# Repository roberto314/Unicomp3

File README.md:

# UNICOMP #

Version 3.00

A modular 8-bit Computer able to recreate (nearly) every microcomputer of the mid 70s to early 80s 
in Hardware without FPGAs (although an FPGA can be added). Can also be used as a teaching tool for:

* VHDL or Verilog
* C
* RTOS (STM32F401 runs ChibiOS. Link: https://www.chibios.org)
* Python
* bash and linux in general (Olimex board runs linux with fbterm and tmux)
* Harwaredesign
* Timing of CPUs
* maybe Assembler
* SPI and I2C Interfaces
* CPLDs and FPGAs

It is different from other designs because of these points:

* it uses a 3.3V only Bus,
* it uses fast RAM for 16 chipselect outputs with single address resolution over the whole 1MB range,
* it uses one SRAM for RAM and ROM replacement (can be write writeprotected) with 1MB,
* it uses a clock generator chip (DS1085) - no more crystals to change,
* it is configureable via STM32 (RAM and ROM content, Clock frequency, chip select lines),
* it can program the CPLDs (only XC9572 and XC9536 tested) from the STM32, no external programmer needed.
* Board size is 100mm x 100mm - no backplane (like the PC/104 standard. Link: https://en.wikipedia.org/wiki/PC/104).
* and maybe most convenient: it can change RAM and ROM content on the fly without crashing the CPU. 
  For example starting the Apple I, going into Basic and uploading the program in about half a second is really nice.

Unicomp plus Logic Analyzer:

### Unicomp modules ###

* USB-Serial board:
	- a simple board with an universal 4x USB to UART module from ebay (FT4232).

* CPU board:
	- can be any 8-bit CPU (6502, 6802, 6809, 68008, 6803, 8051,...)
	- a CPLD (XC9572) for clock generation and glue logic

* Multi Serial boaŕd:
	- suggested chip select #0
	- can be used with the following serial interface chips: MC6850, MOS6551, MOS6552 or pin compatible

* Multi Parallel boaŕd:
	- suggested chip select #1
	- can be used with the following parallel interface chips: MC6820, MC6821, MOS6520, MOS6521, MOS6522, MOS6526, MOS8520, MOS6532 in the first slot
    - the first slot can additionally mimic a MOS6530
	- the second slot can accommodate a MOS6522 or pin compatible

* RAMROM board:
	- chip select fixed at #15 (for chipselect RAM or ROM) and #14 for Write Disable (High for ROM),
	- 1M of SRAM plus an extra 16-bit RAM for address decoding,
	- a STM32F401 'blackpill' board to fill the SRAMs with data over USB,
	- USB shell on the STM32 to change ROM content on the fly,
	- also configures the Address Range of all peripheral modules,
	- acts as a XSVF Player to program the CPLDs

* Prototype board:
	- empty board for prototyping
	- no CPLD

* MAX-II (EPM240) board:
	- CPLD plus Buffers

* self made module:
	- chip select can be any non-used line in the Range from 0 to 13.
	- size is 100mm x 100mm
	- there is the prototype board in the repository for the position of the connectors and also the labels (pinout)

### Configuration RAM ###

The configuration is done with 1Mx16 fast ram on the RAMROM board. It is configured from the STM32F401.
The cs = 15 is for writing the main RAM, cs = 14 is the Write Disable.
The rest is free.

### Working Recreations of old computers (tested again with Unicomp3) ###

| Name                     | prim. IO    | chips used                    | os                               | weblink                                                                 |
|--------------------------|-------------|-------------------------------|----------------------------------|-------------------------------------------------------------------------|
| Motorola MEK D2          | serial      | MC6802, MĆ6850                | newbug, xswtbug, mondeb          |Link: https://www.retrotechnology.com/restore/smithbug.html              |
| Motorola MEK D1          | serial      | MC6802, MĆ6821 (plus Arduino) | Mikbug                           |Link: https://www.retrotechnology.com/restore/smithbug.html              |
| SWTPC 6800               | serial      | MC6802, MĆ6821 (plus Arduino) | Mikbug                           |Link: https://deramp.com/swtpc.com/                                      |
| SWTPC 6800               | serial      | MC6802, MĆ6850                | SWTBUG, SWTBUGA, Mondeb, xSWTBUG |Link: https://deramp.com/swtpc.com/                                      |
| Heathkit ET3400          | serial      | MC6802, MĆ6850                | MITS BASIC, TSC MicroBASIC,...   |Link: https://github.com/jefftranter                                     |
| HD6303 Board (Eric Klaus)| serial      | HD6303 or MC6803              | Monitor +BASIC                   |Link: https://sites.google.com/site/ericmklaus/projects-1/hd6303cpuboard |
| MC3 Computer             | serial      | HD6303 or MC6803              | Monitor                          |Link: https://www.waveguide.se/?article=mc3-a-diy-8-bit-computer         |
| Grant Searle 6809 board  | serial      | MC6809E, MC6850               | MS Basic                         |Link: http://searle.x10host.com/6809/Simple6809.html                     |
| Grant Searle 6502 board  | serial      | MOS6502, MC6850               | OSI Basic                        |Link: http://searle.x10host.com/6502/Simple6502.html                     |
| Daryl Rictor 6502 board  | serial      | MOS6502, R6551                | SBC-2 (monitor only)             |Link: https://sbc.rictor.org/info2.html                                  |
| Daryl Rictor 6502 board  | serial      | MOS6502, MC6850               | SBC-2 (monitor only)             |Link: https://sbc.rictor.org/info2.html                                  |
| SYM1                     | serial      | MOS6502, UM6532               | SYM1 ( +BASIC +RAE)              |Link: http://retro.hansotten.nl/6502-sbc/synertek-sym-ktm/sym-1/         |
| KIM1                     | serial      | MOS6502, UM6532               | KIM1                             |Link: http://retro.hansotten.nl/6502-sbc/kim-1-manuals-and-software/     |
| Apple I                  | serial      | MOS6502, MĆ6821 (plus Arduino)| Wozmon + BASIC                   |Link: http://retro.hansotten.nl/6502-sbc/apple-1/                        |
| DREAM 6800               | BAS (Video) | MC6802, MAX-II                | DREAM operating System (Chip8)   |Link: http://www.mjbauer.biz/DREAM6800.htm                               |
| Psion Organizer I        | LCD         | HD6303                        | Psion OS                         |Link: https://www.jaapsch.net/psion/index.htm                            |

### python helper scripts ###

* UC3_upload.py: multi-function script. up- or download RAM Content, write or read the clock chip, set the reset pin, upload configuration data from file, upload RAM data from file, gets version number, 

* UC3_make_uploadfile.py: creates an .ucb file for upload. It can have multiple RAM locations and lengths.

### CPLD programming ###

* compiling the vhdl (or verilog) code must be done on a computer with the Xilinx ISE 14.7 toolchain installed.
 Link: https://www.xilinx.com/support/download/index.html/content/xilinx/en/downloadNav/vivado-design-tools/archive-ise.html

* compiling itself can be done inside ISE or with the supplied makefile (look inside the bord directory in cpld firmware)

* a simple **make** will compile the firmware and a **make prog** will transfer the file to the stm32 for programming.

### Used Software and OS ###

* Linux Mint (21.3 cinnamon) (Link: https://linuxmint.com/)
* Sublime Text 3 (Link: https://www.sublimetext.com/)
* 010 Editor (Hex Editor) (Link: https://www.sweetscape.com/010editor/)
* Chibi Studio 20 (IDE for ChibiOS) (Link: https://www.chibios.org/dokuwiki/doku.php?id=chibios:products:chibistudio:start)
* Wavedrom (2.9.1) (Link: https://wavedrom.com/)
* Pulseview (0.5.0-nightly Appimaage) (Part of sigrok) (Link: https://sigrok.org/wiki/PulseView)
* Logisim-Evolution (3.8.0) (Link: https://github.com/logisim-evolution/logisim-evolution)
* Quartus (13.0.1 Build232 Web Edition - 64 Bit) for MAX-II
* Xilinx ISE (14.7 - 64 Bit) for XC9572

### Used Hardware ###

* Oscilloscope: Rigol DS1054Z (4 channel)
* Logic Analyzer: Hantek 4032L (32 channel)

### History Lesson ###

The unicomp Project started a couple of years ago and is developed in my spare time. It is intended to be a module system to test out different hardware configurations or CPLD- or FPGA- extensions and to recreate old systems and test software and operating systems.

Differences Unicomp2 from Unicomp1:

* chipselect not with CPLD but with RAM on every peripheral board - more flexible,
* chipselect resolution improved to two,

Differences Unicomp3 from Unicomp2:

* chipselect RAM is on RAMROM Board (16-bit wide) - that leads to:
* simpler (and cheaper) peripheral modules,
* no linux SBC needed,
* CPLD programming from STM32 or with external programmer (JTAG Header on every CPU Module)
* 3.3V Supply on RAMROM board,
* RAM has now a backup battery (CR2032) battery,
* improved documentation.

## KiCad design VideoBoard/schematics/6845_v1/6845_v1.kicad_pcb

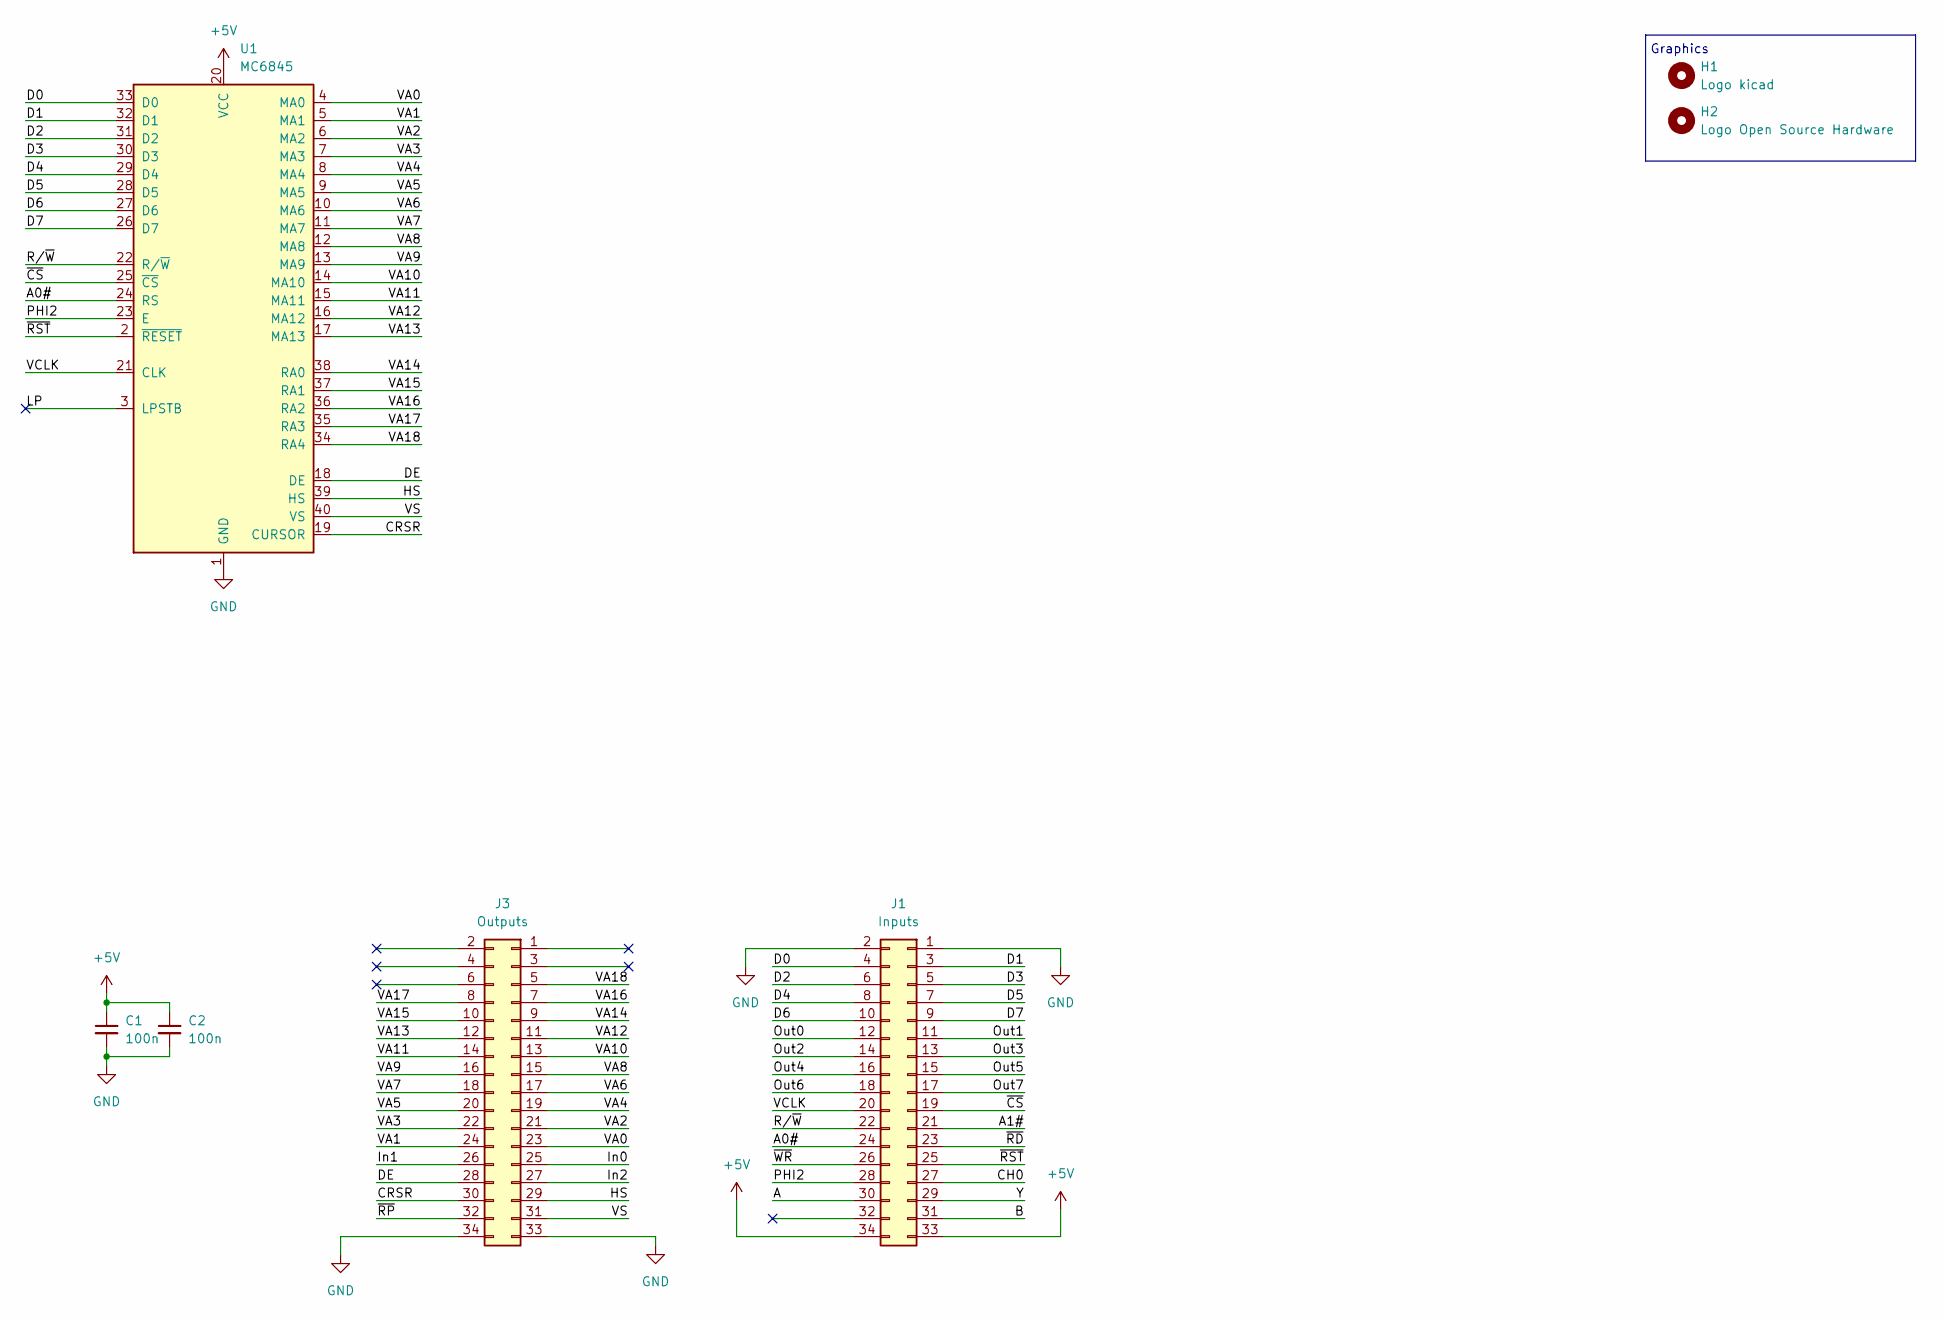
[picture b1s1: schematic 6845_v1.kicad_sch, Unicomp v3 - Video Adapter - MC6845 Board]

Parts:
C1, C2: 100n; C_1206_3216Metric_Pad1.33x1.80mm_HandSolder
H1: Logo kicad; KiCad-Logo2_6mm_SilkScreen
H2: Logo Open Source Hardware; OSHW-Logo2_7.3x6mm_SilkScreen
J1: Inputs; PinHeader_2x17_P2.54mm_Vertical
J3: Outputs; PinHeader_2x17_P2.54mm_Vertical
U1: MC6845; DIP-40_W15.24mm

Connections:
+5V: C1.1, C2.1, J1.33, J1.34, U1.20 (VCC)
/A: J1.30
/A0#: J1.24, U1.24 (RS)
/A1#: J1.21
/B: J1.31
/CH0: J1.27
/CRSR: J3.30, U1.19 (CURSOR)
/D0: J1.4, U1.33 (D0)
/D1: J1.3, U1.32 (D1)
/D2: J1.6, U1.31 (D2)
/D3: J1.5, U1.30 (D3)
/D4: J1.8, U1.29 (D4)
/D5: J1.7, U1.28 (D5)
/D6: J1.10, U1.27 (D6)
/D7: J1.9, U1.26 (D7)
/DE: J3.28, U1.18 (DE)
/HS: J3.29, U1.39 (HS)
/In0: J3.25
/In1: J3.26
/In2: J3.27
/LP: U1.3 (LPSTB)
/Out0: J1.12
/Out1: J1.11
/Out2: J1.14
/Out3: J1.13
/Out4: J1.16
/Out5: J1.15
/Out6: J1.18
/Out7: J1.17
/PHI2: J1.28, U1.23 (E)
/R/~W: J1.22, U1.22 (R/~W)
/VA0: J3.23, U1.4 (MA0)
/VA1: J3.24, U1.5 (MA1)
/VA2: J3.21, U1.6 (MA2)
/VA3: J3.22, U1.7 (MA3)
/VA4: J3.19, U1.8 (MA4)
/VA5: J3.20, U1.9 (MA5)
/VA6: J3.17, U1.10 (MA6)
/VA7: J3.18, U1.11 (MA7)
/VA8: J3.15, U1.12 (MA8)
/VA9: J3.16, U1.13 (MA9)
/VA10: J3.13, U1.14 (MA10)
/VA11: J3.14, U1.15 (MA11)
/VA12: J3.11, U1.16 (MA12)
/VA13: J3.12, U1.17 (MA13)
/VA14: J3.9, U1.38 (RA0)
/VA15: J3.10, U1.37 (RA1)
/VA16: J3.7, U1.36 (RA2)
/VA17: J3.8, U1.35 (RA3)
/VA18: J3.5, U1.34 (RA4)
/VCLK: J1.20, U1.21 (CLK)
/VS: J3.31, U1.40 (VS)
/Y: J1.29
/~CS: J1.19, U1.25 (~CS)
/~RD: J1.23
/~RP: J3.32
/~RST: J1.25, U1.2 (~RESET)
/~WR: J1.26
GND: C1.2, C2.2, J1.1, J1.2, J3.33, J3.34, U1.1 (GND)

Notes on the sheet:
Graphics

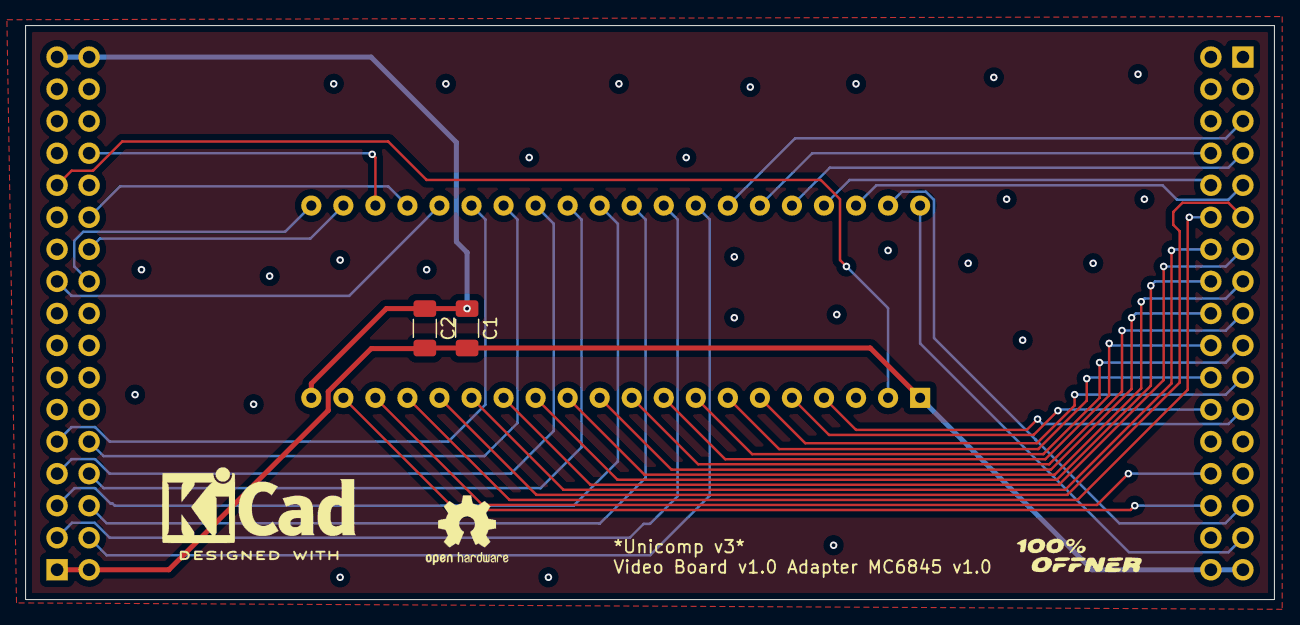
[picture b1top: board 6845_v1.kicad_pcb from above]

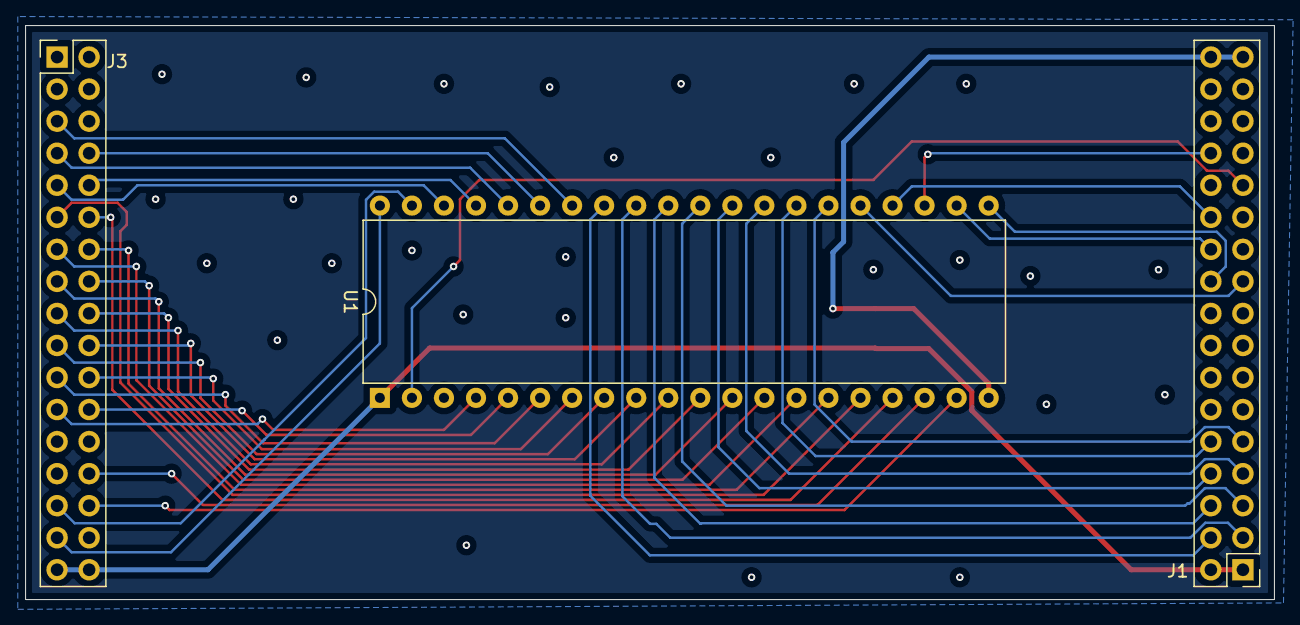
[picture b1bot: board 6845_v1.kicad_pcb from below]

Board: 2 copper layers, 99.0 x 45.5 mm, 7 parts (3 on the bottom side), 39 nets.

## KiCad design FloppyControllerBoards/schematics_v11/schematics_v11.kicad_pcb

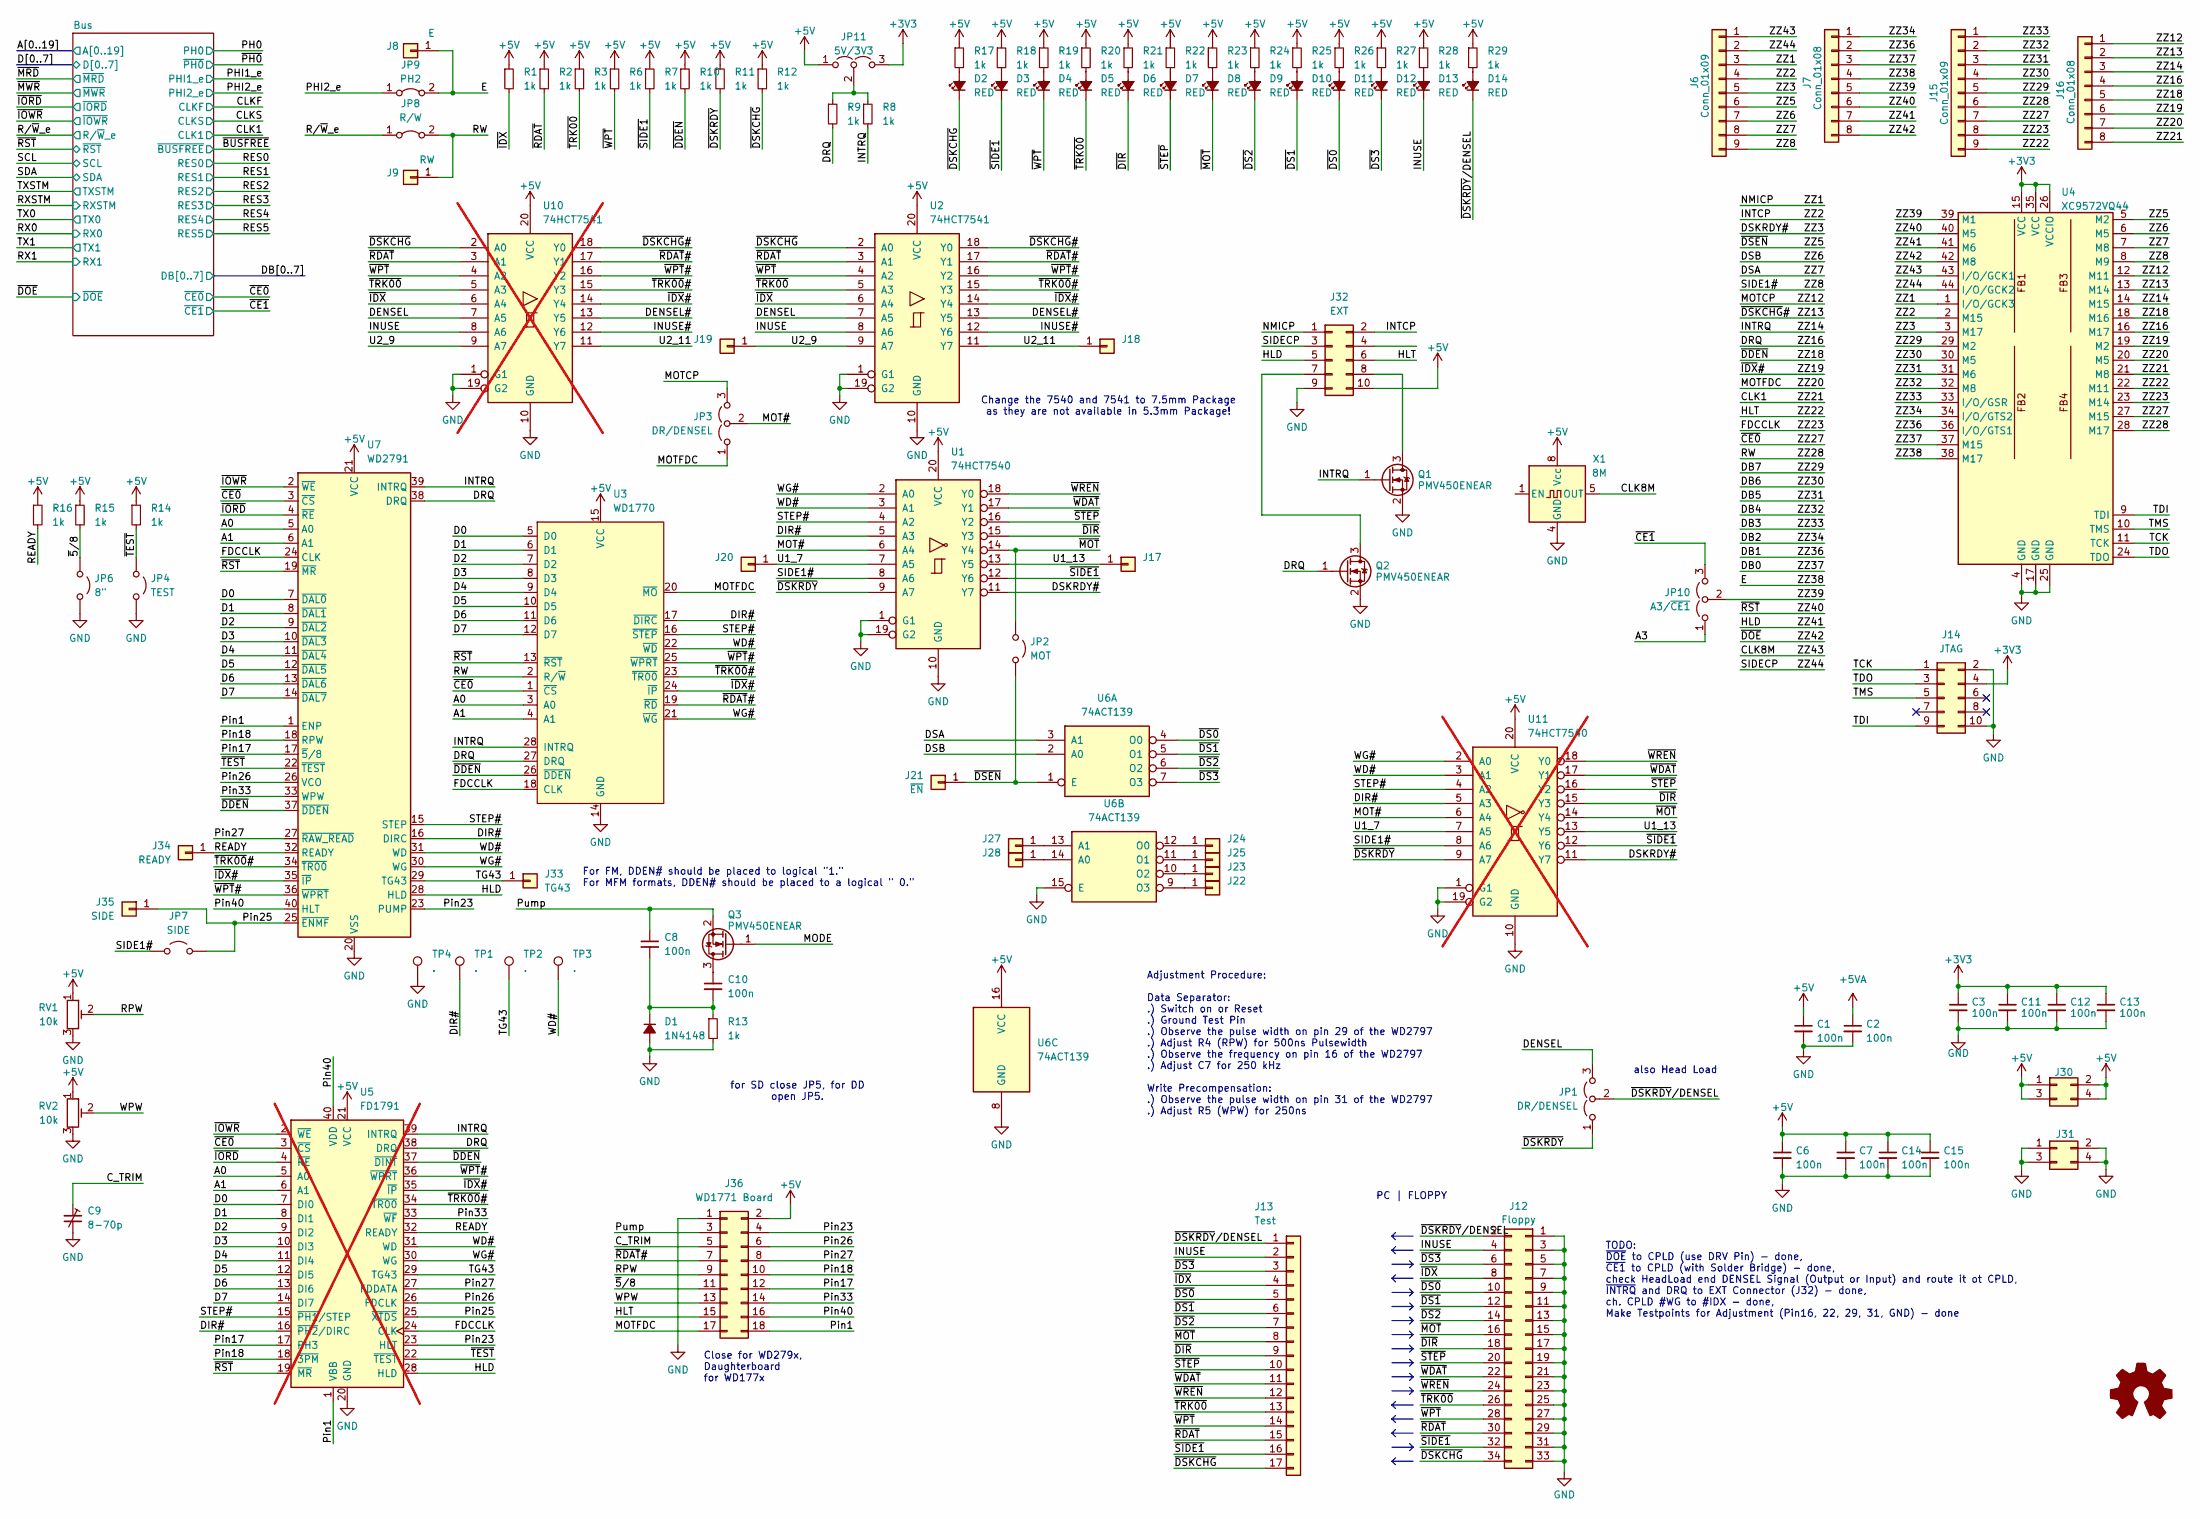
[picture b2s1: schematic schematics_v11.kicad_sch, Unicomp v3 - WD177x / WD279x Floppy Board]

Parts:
C1, C2, C3, C6, C7, C8, C10, C11, C12, C13, C14, C15: 100n; C_1206_3216Metric
C9: 8-70p; Capacitor_Trim
D1: 1N4148; D_1206_3216Metric_Pad1.42x1.75mm_HandSolder
D2, D3, D4, D5, D6, D7, D8, D9, D10, D11, D12, D13, D14: RED; LED_1206_3216Metric_Pad1.42x1.75mm_HandSolder
J6, J15: Conn_01x09; PinHeader_1x09_P2.54mm_Vertical
J7, J16: Conn_01x08; PinHeader_1x08_P2.54mm_Vertical
J8: E; PinHeader_1x01_P2.00mm_Vertical
J9: RW; PinHeader_1x01_P2.00mm_Vertical
J12: Floppy; PinHeader_2x17_P2.54mm_Horizontal
J13: Test; PinSocket_1x17_P2.54mm_Vertical
J14: JTAG; PinHeader_2x05_P2.54mm_Horizontal
J17, J18, J19, J20, J22, J23, J24, J25, J27, J28: Conn_01x01; PinHeader_1x01_P1.27mm_Vertical
J21: ~{EN}; PinHeader_1x01_P1.27mm_Vertical
J30, J31: Conn_02x02_Odd_Even; PinSocket_2x02_P2.54mm_Vertical
J32: EXT; PinHeader_2x05_P2.54mm_Horizontal
J33: TG43; PinHeader_1x01_P1.27mm_Vertical
J34: READY; PinHeader_1x01_P1.27mm_Vertical
J35: SIDE; PinHeader_1x01_P1.27mm_Vertical
J36: WD1771 Board; PinHeader_2x09_P2.54mm_Vertical
JP1, JP3: DR/DENSEL; PinHeader_1x03_P2.54mm_Vertical
JP2: MOT; SolderJumper-2_P1.3mm_Open_RoundedPad1.0x1.5mm
JP4: TEST; PinHeader_1x02_P2.54mm_Vertical
JP6: 8"; PinHeader_1x02_P2.54mm_Vertical
JP7: SIDE; SolderJumper-2_P1.3mm_Open_RoundedPad1.0x1.5mm
JP8: R/W; SolderJumper-2_P1.3mm_Bridged_RoundedPad1.0x1.5mm
JP9: PH2; SolderJumper-2_P1.3mm_Bridged_RoundedPad1.0x1.5mm
JP10: A3/~{CE1}; SolderJumper-3_P1.3mm_Open_RoundedPad1.0x1.5mm
JP11: 5V/3V3; SolderJumper-3_P1.3mm_Open_RoundedPad1.0x1.5mm
Q1, Q2, Q3: PMV450ENEAR; SOT-23
R1, R2, R3, R6, R7, R8, R9, R10, R11, R12, R13, R14, R15, R16, R17, R18, R19, R20, R21, R22, R23, R24, R25, R26, R27, R28, R29: 1k; R_1206_3216Metric_Pad1.30x1.75mm_HandSolder
RV1, RV2: 10k; Potentiometer_Vishay_T73XW_Horizontal
TP1, TP2, TP3, TP4: .; PinHeader_1x01_P2.54mm_Vertical
U1: 74HCT7540; SO-20_5.3x12.6mm_P1.27mm
U2: 74HCT7541; SO-20_5.3x12.6mm_P1.27mm
U3: WD1770; DIP-28_W15.24mm_Socket
U4: XC9572VQ44; TQFP-44_10x10mm_P0.8mm
U5: FD1791; DIP-40_W15.24mm; not fitted
U6: 74ACT139; SOIC-16_3.9x9.9mm_P1.27mm
U7: WD2791; DIP-40_W15.24mm
U10: 74HCT7541; SO-20_12.8x7.5mm_P1.27mm; not fitted
U11: 74HCT7540; SO-20_12.8x7.5mm_P1.27mm; not fitted
X1: 8M; Oscillator_DIP-8

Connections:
+3V3: C3.1, C11.1, C12.1, C13.1, J14.4, JP11.3 (B), U4.15 (VCC), U4.26 (VCCIO), U4.35 (VCC); also elsewhere on the board
+5V: C1.1, C6.1, C7.1, C14.1, C15.1, J30.1, J30.2, J30.3, J30.4, J32.10, J36.2, JP11.1 (A), R1.1, R2.1, R3.1, R6.1, R7.1, R10.1, R11.1, R12.1, R14.1, R15.1, R16.1, R17.1, R18.1, R19.1, R20.1, R21.1, R22.1, R23.1, R24.1, R25.1, R26.1, R27.1, R28.1, R29.1, RV1.1, RV2.1, U1.20 (VCC), U2.20 (VCC), U3.15 (VCC), U5.21 (VCC), U6.16 (VCC), U7.21 (VCC), U10.20 (VCC), U11.20 (VCC), X1.8 (Vcc); also elsewhere on the board
+5VA: C2.1; also elsewhere on the board
/A0: U3.3 (A0), U5.5 (A0), U7.5 (A0); also elsewhere on the board
/A1: U3.4 (A1), U5.6 (A1), U7.6 (A1); also elsewhere on the board
/A3: JP10.1 (A); also elsewhere on the board
/CLK1: J16.8, U4.21 (M8); also elsewhere on the board
/CLK8M: J6.1, U4.43 (I/O/GCK1), X1.5 (OUT)
/C_TRIM: C9.1, J36.5
/D0: U3.5 (D0), U5.7 (DI0), U7.7 (~DAL0); also elsewhere on the board
/D1: U3.6 (D1), U5.8 (DI1), U7.8 (~DAL1); also elsewhere on the board
/D2: U3.7 (D2), U5.9 (DI2), U7.9 (~DAL2); also elsewhere on the board
/D3: U3.8 (D3), U5.10 (DI3), U7.10 (~DAL3); also elsewhere on the board
/D4: U3.9 (D4), U5.11 (DI4), U7.11 (~DAL4); also elsewhere on the board
/D5: U3.10 (D5), U5.12 (DI5), U7.12 (~DAL5); also elsewhere on the board
/D6: U3.11 (D6), U5.13 (DI6), U7.13 (~DAL6); also elsewhere on the board
/D7: U3.12 (D7), U5.14 (DI7), U7.14 (~DAL7); also elsewhere on the board
/DB0: J7.3, U4.37 (M15); also elsewhere on the board
/DB1: J7.2, U4.36 (I/O/GTS1); also elsewhere on the board
/DB2: J7.1, U4.34 (I/O/GTS2); also elsewhere on the board
/DB3: J15.1, U4.33 (I/O/GSR); also elsewhere on the board
/DB4: J15.2, U4.32 (M8); also elsewhere on the board
/DB5: J15.3, U4.31 (M6); also elsewhere on the board
/DB6: J15.4, U4.30 (M5); also elsewhere on the board
/DB7: J15.5, U4.29 (M2); also elsewhere on the board
/DENSEL: JP1.3 (B), U2.7 (A5), U10.7 (A5)
/DENSEL#: U2.13 (Y5), U10.13 (Y5)
/DIR#: TP1.1, U1.5 (A3), U3.17 (~DIRC), U5.16 (~PH2/DIRC), U7.16 (DIRC), U11.5 (A3)
/DRQ: J16.4, Q2.1 (G), R9.2, U3.27 (DRQ), U4.16 (M17), U5.38 (DRQ), U7.38 (DRQ)
/DSA: J6.8, U4.7 (M8), U6.3 (A1)
/DSB: J6.7, U4.6 (M5), U6.2 (A0)
/DSKRDY#: J6.5, U1.11 (Y7), U4.3 (M17), U11.11 (Y7)
/E: J7.4, J8.1, JP9.2 (B), U4.38 (M17)
/FDCCLK: J15.8, U3.18 (CLK), U4.23 (M14), U5.24 (CLK), U7.24 (CLK)
/HLD: J7.7, J32.5, U4.41 (M6), U5.28 (HLD), U7.28 (HLD)
/HLT: J15.9, J32.6, J36.15, U4.22 (M11)
/INTCP: J6.4, J32.2, U4.2 (M15)
/INTRQ: J16.3, Q1.1 (G), R8.2, U3.28 (INTRQ), U4.14 (M15), U5.39 (INTRQ), U7.39 (INTRQ)
/INUSE: D13.1 (K), J12.4, J13.2, U2.8 (A6), U10.8 (A6)
/INUSE#: U2.12 (Y6), U10.12 (Y6)
/MODE: Q3.1 (G)
/MOT#: JP3.2 (C), U1.6 (A4), U11.6 (A4)
/MOTCP: J16.1, JP3.3 (B), U4.12 (M11)
/MOTFDC: J16.7, J36.17, JP3.1 (A), U3.20 (~MO), U4.20 (M5)
/NMICP: J6.3, J32.1, U4.1 (I/O/GCK3)
/PHI2_e: JP9.1 (A); also elsewhere on the board
/Pin1: J36.18, U5.1 (VBB), U7.1 (ENP)
/Pin17: J36.12, U5.17 (PH3), U7.17 (~5/8)
/Pin18: J36.10, U5.18 (~3PM), U7.18 (RPW)
/Pin23: J36.4, U5.23 (HLT), U7.23 (PUMP)
/Pin25: J35.1, JP7.2 (B), U5.25 (~XTDS), U7.25 (~ENMF)
/Pin26: J36.6, U5.26 (FDCLK), U7.26 (VCO)
/Pin27: J36.8, U5.27 (FDDATA), U7.27 (~RAW_READ)
/Pin33: J36.14, U5.33 (~WF), U7.33 (WPW)
/Pin40: J36.16, U5.40 (VDD), U7.40 (HLT)
/Pump: C8.1, J36.3, Q3.2 (S)
/READY: J34.1, R16.2, U5.32 (READY), U7.32 (READY)
/RPW: J36.9, RV1.2
/RW: J9.1, J15.6, JP8.2 (B), U3.2 (R/~W), U4.28 (M17)
/R/~W_e: JP8.1 (A); also elsewhere on the board
/SIDE1#: J6.9, JP7.1 (A), U1.8 (A6), U4.8 (M9), U11.8 (A6)
/SIDECP: J6.2, J32.3, U4.44 (I/O/GCK2)
/STEP#: U1.4 (A2), U3.16 (~STEP), U5.15 (~PH1/STEP), U7.15 (STEP), U11.4 (A2)
/TCK: J14.1, U4.11 (TCK)
/TDI: J14.9, U4.9 (TDI)
/TDO: J14.3, U4.24 (TDO)
/TG43: J33.1, TP2.1, U5.29 (TG43), U7.29 (TG43)
/TMS: J14.5, U4.10 (TMS)
/U1_7: J20.1, U1.7 (A5), U11.7 (A5)
/U1_13: J17.1, U1.13 (Y5), U11.13 (Y5)
/U2_9: J19.1, U2.9 (A7), U10.9 (A7)
/U2_11: J18.1, U2.11 (Y7), U10.11 (Y7)
/WD#: TP3.1, U1.3 (A1), U3.22 (~WD), U5.31 (WD), U7.31 (WD), U11.3 (A1)
/WG#: U1.2 (A0), U3.21 (~WG), U5.30 (WG), U7.30 (WG), U11.2 (A0)
/WPW: J36.13, RV2.2
/ZZ5: J6.6, J21.1, JP2.2 (B), U4.5 (M2), U6.1 (E)
/ZZ13: J16.2, U2.18 (Y0), U4.13 (M14), U10.18 (Y0)
/ZZ18: J16.5, R10.2, U3.26 (~DDEN), U4.18 (M16), U5.37 (~DINT), U7.37 (~DDEN)
/ZZ19: J16.6, U2.14 (Y4), U3.24 (~IP), U4.19 (M2), U5.35 (~IP), U7.35 (~IP), U10.14 (Y4)
/ZZ27: J15.7, U3.1 (~CS), U4.27 (M15), U5.3 (~CS), U7.3 (~CS); also elsewhere on the board
/ZZ39: J7.5, JP10.2 (C), U4.39 (M1)
/ZZ40: J7.6, U3.13 (~RST), U4.40 (M5), U5.19 (~MR), U7.19 (~MR); also elsewhere on the board
/ZZ42: J7.8, U4.42 (M8); also elsewhere on the board
/~5/8: J36.11, JP6.1 (A), R15.2
/~CE1: JP10.3 (B); also elsewhere on the board
/~DIR: D6.1 (K), J12.18, J13.9, U1.15 (Y3), U11.15 (Y3)
/~DS0: D11.1 (K), J12.10, J13.5, U6.4 (O0)
/~DS1: D10.1 (K), J12.12, J13.6, U6.5 (O1)
/~DS2: D9.1 (K), J12.14, J13.7, U6.6 (O2)
/~DS3: D12.1 (K), J12.6, J13.3, U6.7 (O3)
/~DSKCHG: D2.1 (K), J12.34, J13.17, R12.2, U2.2 (A0), U10.2 (A0)
/~DSKRDY: JP1.1 (A), R11.2, U1.9 (A7), U11.9 (A7)
/~DSKRDY/DENSEL: D14.1 (K), J12.2, J13.1, JP1.2 (C)
/~IDX: J12.8, J13.4, R1.2, U2.6 (A4), U10.6 (A4)
/~IORD: U5.4 (~RE), U7.4 (~RE); also elsewhere on the board
/~IOWR: U5.2 (~WE), U7.2 (~WE); also elsewhere on the board
/~MOT: D8.1 (K), J12.16, J13.8, JP2.1 (A), U1.14 (Y4), U11.14 (Y4)
/~RDAT: J12.30, J13.15, R2.2, U2.3 (A1), U10.3 (A1)
/~RDAT#: J36.7, U2.17 (Y1), U3.19 (~RD), U10.17 (Y1)
/~SIDE1: D3.1 (K), J12.32, J13.16, R7.2, U1.12 (Y6), U11.12 (Y6)
/~STEP: D7.1 (K), J12.20, J13.10, U1.16 (Y2), U11.16 (Y2)
/~TEST: JP4.1 (A), R14.2, U5.22 (~TEST), U7.22 (~TEST)
/~TRK00: D5.1 (K), J12.26, J13.13, R3.2, U2.5 (A3), U10.5 (A3)
/~TRK00#: U2.15 (Y3), U3.23 (~TR00), U5.34 (~TR00), U7.34 (~TR00), U10.15 (Y3)
/~WDAT: J12.22, J13.11, U1.17 (Y1), U11.17 (Y1)
/~WPT: D4.1 (K), J12.28, J13.14, R6.2, U2.4 (A2), U10.4 (A2)
/~WPT#: U2.16 (Y2), U3.25 (~WPRT), U5.36 (~WPRT), U7.36 (~WPRT), U10.16 (Y2)
/~WREN: J12.24, J13.12, U1.18 (Y0), U11.18 (Y0)
unnamed: C8.2, C10.2, D1.1 (K), R13.1
unnamed: D2.2 (A), R17.2
unnamed: D3.2 (A), R18.2
unnamed: D4.2 (A), R19.2
unnamed: D5.2 (A), R20.2
unnamed: D6.2 (A), R21.2
unnamed: D7.2 (A), R22.2
unnamed: D8.2 (A), R23.2
unnamed: D9.2 (A), R24.2
unnamed: D10.2 (A), R25.2
unnamed: D11.2 (A), R26.2
unnamed: D12.2 (A), R27.2
unnamed: D13.2 (A), R28.2
unnamed: D14.2 (A), R29.2
unnamed: J22.1, U6.9 (O3)
unnamed: J23.1, U6.10 (O2)
unnamed: J24.1, U6.12 (O0)
unnamed: J25.1, U6.11 (O1)
unnamed: J27.1, U6.13 (A1)
unnamed: J28.1, U6.14 (A0)
unnamed: J32.7, Q2.3 (D)
unnamed: J32.8, Q1.3 (D)
unnamed: JP11.2 (C), R8.1, R9.1
unnamed: C10.1, Q3.3 (D)

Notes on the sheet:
Adjustment Procedure: Data Separator: .) Switch on or Reset .) Ground Test Pin .) Observe the pulse width on pin 29 of the WD2797 .) Adjust R4 (RPW) for 500ns Pulsewidth .) Observe the frequency on pin 16 of the WD2797 .) Adjust C7 for 250 kHz Write Precompensation: .) Observe the pulse width on pi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
Close for WD279x, Daughterboard for WD177x
also Head Load
TODO: ~{DOE} to CPLD (use DRV Pin) - done, ~{CE1} to CPLD (with Solder Bridge) - done, check HeadLoad end DENSEL Signal (Output or Input) and route it ot CPLD, ~{INTRQ} and DRQ to EXT Connector (J32) - done, ch. CPLD #WG to #IDX - done, Make Testpoints for Adjustment (Pin16, 22, 29, 31, GND) - done
Change the 7540 and 7541 to 7.5mm Package as they are not available in 5.3mm Package!
for SD close JP5, for DD open JP5.
For FM, DDEN# should be placed to logical "1." For MFM formats, DDEN# should be placed to a logical " 0."
PC | FLOPPY

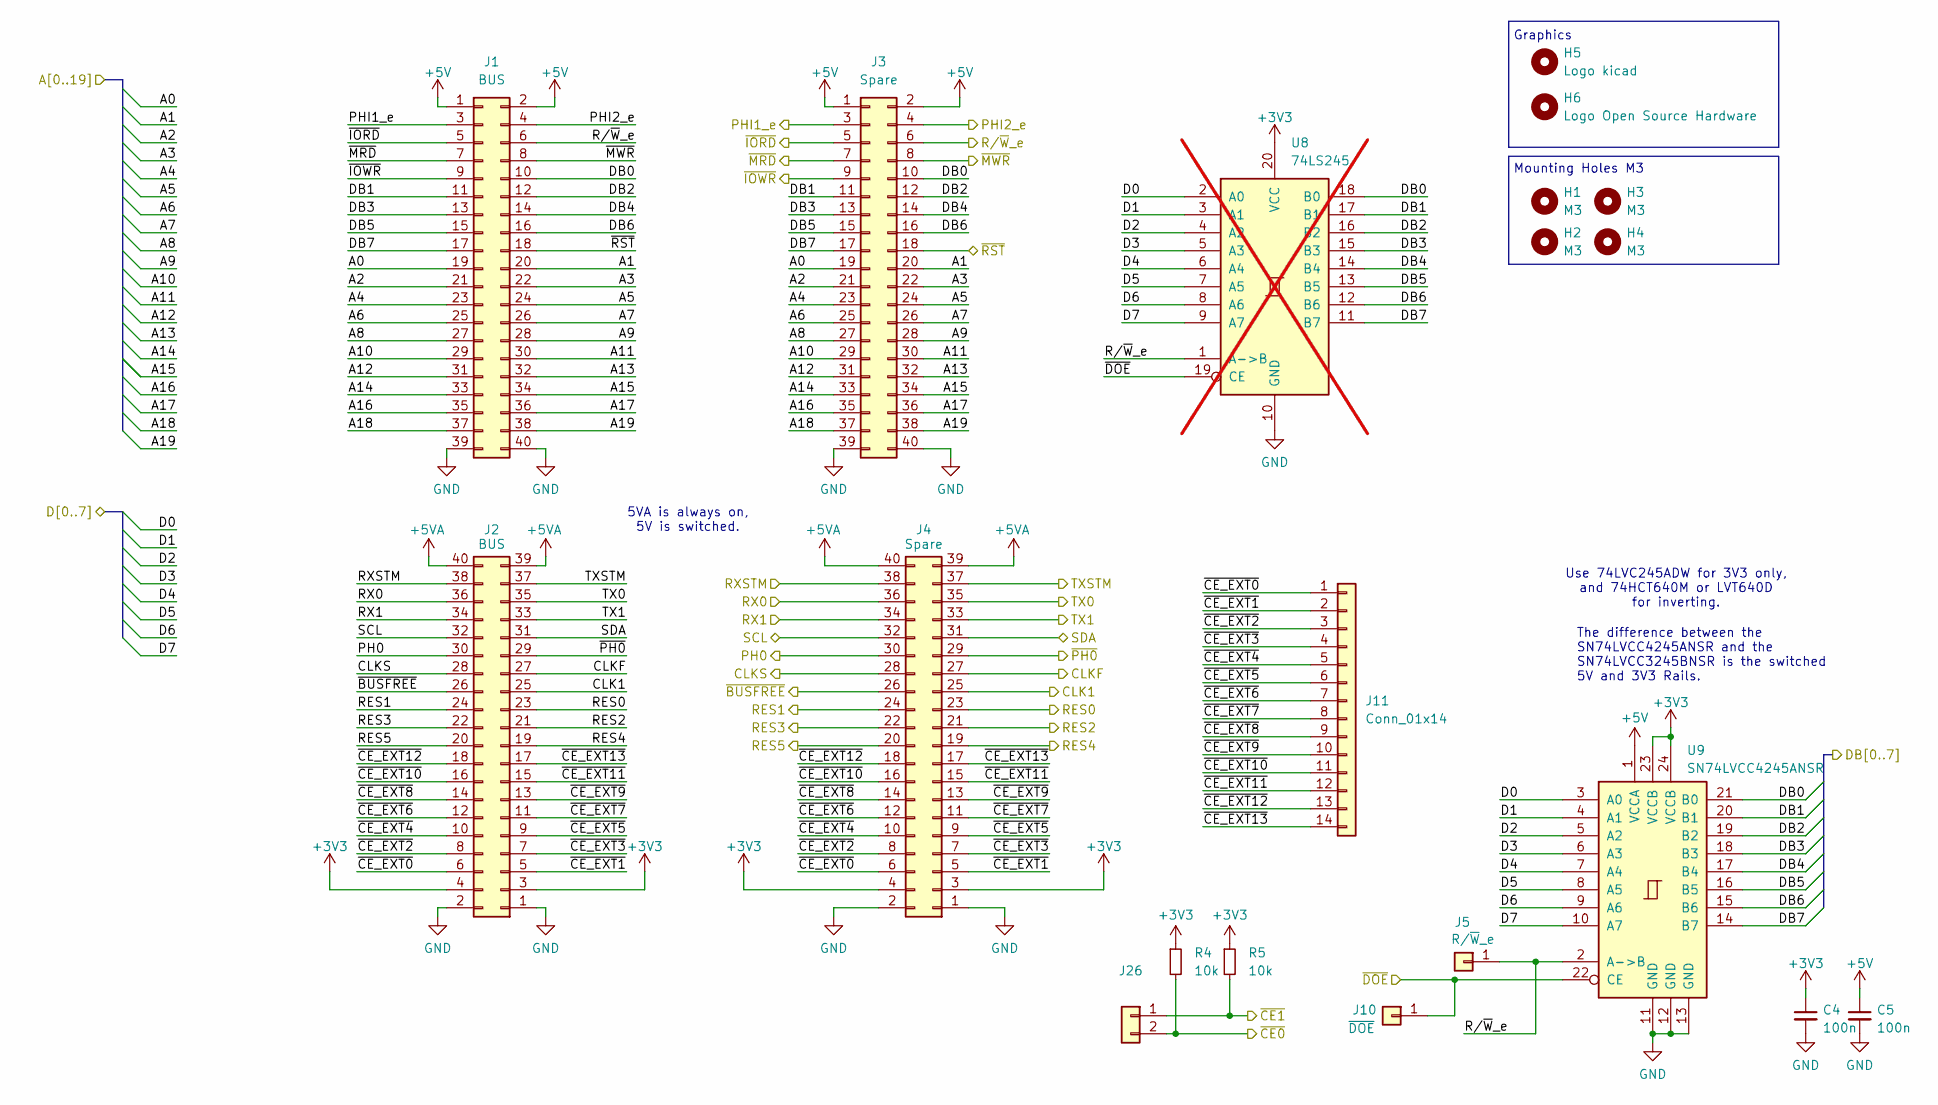
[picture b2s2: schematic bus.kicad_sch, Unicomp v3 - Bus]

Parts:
C4, C5: 100n; C_1206_3216Metric
H1, H2, H3, H4: M3; MountingHole_3.2mm_M3
H5: Logo kicad; KiCad-Logo2_6mm_SilkScreen
H6: Logo Open Source Hardware; OSHW-Logo2_7.3x6mm_SilkScreen
J1, J2: BUS; PinSocket_2x20_P2.54mm_Vertical
J3, J4: Spare; PinSocket_2x20_P2.54mm_Vertical
J5: R/~{W}_e; PinHeader_1x01_P2.00mm_Vertical
J10: ~{DOE}; PinHeader_1x01_P2.00mm_Vertical
J11: Conn_01x14; PinSocket_1x14_P2.54mm_Vertical
J26: Conn_01x02; PinSocket_1x02_P2.54mm_Vertical
R4, R5: 10k; R_1206_3216Metric_Pad1.30x1.75mm_HandSolder
U8: 74LS245; SOIC-20W_7.5x12.8mm_P1.27mm; not fitted
U9: SN74LVCC4245ANSR; SO-24_5.3x15mm_P1.27mm

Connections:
+3V3: C4.1, J2.3, J2.4, J4.3, J4.4, R4.1, R5.1, U8.20 (VCC), U9.23 (VCCB), U9.24 (VCCB); also elsewhere on the board
+5V: C5.1, J1.1, J1.2, J3.1, J3.2, U9.1 (VCCA); also elsewhere on the board
+5VA: J2.39, J2.40, J4.39, J4.40; also elsewhere on the board
/A0: J1.19, J3.19; also elsewhere on the board
/A1: J1.20, J3.20; also elsewhere on the board
/A2: J1.21, J3.21
/A3: J1.22, J3.22; also elsewhere on the board
/A4: J1.23, J3.23
/A5: J1.24, J3.24
/A6: J1.25, J3.25
/A7: J1.26, J3.26
/A8: J1.27, J3.27
/A9: J1.28, J3.28
/A10: J1.29, J3.29
/A11: J1.30, J3.30
/A12: J1.31, J3.31
/A13: J1.32, J3.32
/A14: J1.33, J3.33
/A15: J1.34, J3.34
/A16: J1.35, J3.35
/A17: J1.36, J3.36
/A18: J1.37, J3.37
/A19: J1.38, J3.38
/Bus/~CE_EXT0: J2.6, J4.6, J11.1
/Bus/~CE_EXT1: J2.5, J4.5, J11.2
/Bus/~CE_EXT2: J2.8, J4.8, J11.3
/Bus/~CE_EXT3: J2.7, J4.7, J11.4
/Bus/~CE_EXT4: J2.10, J4.10, J11.5
/Bus/~CE_EXT5: J2.9, J4.9, J11.6
/Bus/~CE_EXT6: J2.12, J4.12, J11.7
/Bus/~CE_EXT7: J2.11, J4.11, J11.8
/Bus/~CE_EXT8: J2.14, J4.14, J11.9
/Bus/~CE_EXT9: J2.13, J4.13, J11.10
/Bus/~CE_EXT10: J2.16, J4.16, J11.11
/Bus/~CE_EXT11: J2.15, J4.15, J11.12
/Bus/~CE_EXT12: J2.18, J4.18, J11.13
/Bus/~CE_EXT13: J2.17, J4.17, J11.14
/CLK1: J2.25, J4.25; also elsewhere on the board
/CLKF: J2.27, J4.27
/CLKS: J2.28, J4.28
/D0: U8.2 (A0), U9.3 (A0); also elsewhere on the board
/D1: U8.3 (A1), U9.4 (A1); also elsewhere on the board
/D2: U8.4 (A2), U9.5 (A2); also elsewhere on the board
/D3: U8.5 (A3), U9.6 (A3); also elsewhere on the board
/D4: U8.6 (A4), U9.7 (A4); also elsewhere on the board
/D5: U8.7 (A5), U9.8 (A5); also elsewhere on the board
/D6: U8.8 (A6), U9.9 (A6); also elsewhere on the board
/D7: U8.9 (A7), U9.10 (A7); also elsewhere on the board
/DB0: J1.10, J3.10, U8.18 (B0), U9.21 (B0); also elsewhere on the board
/DB1: J1.11, J3.11, U8.17 (B1), U9.20 (B1); also elsewhere on the board
/DB2: J1.12, J3.12, U8.16 (B2), U9.19 (B2); also elsewhere on the board
/DB3: J1.13, J3.13, U8.15 (B3), U9.18 (B3); also elsewhere on the board
/DB4: J1.14, J3.14, U8.14 (B4), U9.17 (B4); also elsewhere on the board
/DB5: J1.15, J3.15, U8.13 (B5), U9.16 (B5); also elsewhere on the board
/DB6: J1.16, J3.16, U8.12 (B6), U9.15 (B6); also elsewhere on the board
/DB7: J1.17, J3.17, U8.11 (B7), U9.14 (B7); also elsewhere on the board
/PH0: J2.30, J4.30
/PHI1_e: J1.3, J3.3
/PHI2_e: J1.4, J3.4; also elsewhere on the board
/RES0: J2.23, J4.23
/RES1: J2.24, J4.24
/RES2: J2.21, J4.21
/RES3: J2.22, J4.22
/RES4: J2.19, J4.19
/RES5: J2.20, J4.20
/RX0: J2.36, J4.36
/RX1: J2.34, J4.34
/RXSTM: J2.38, J4.38
/R/~W_e: J1.6, J3.6, J5.1, U8.1 (A->B), U9.2 (A->B); also elsewhere on the board
/SCL: J2.32, J4.32
/SDA: J2.31, J4.31
/TX0: J2.35, J4.35
/TX1: J2.33, J4.33
/TXSTM: J2.37, J4.37
/ZZ27: J26.2, R4.2; also elsewhere on the board
/ZZ40: J1.18, J3.18; also elsewhere on the board
/ZZ42: J10.1, U8.19 (CE), U9.22 (CE); also elsewhere on the board
/~BUSFREE: J2.26, J4.26
/~CE1: J26.1, R5.2; also elsewhere on the board
/~IORD: J1.5, J3.5; also elsewhere on the board
/~IOWR: J1.9, J3.9; also elsewhere on the board
/~MRD: J1.7, J3.7
/~MWR: J1.8, J3.8
/~PH0: J2.29, J4.29

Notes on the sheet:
Graphics
5VA is always on, 5V is switched.
Use 74LVC245ADW for 3V3 only, and 74HCT640M or LVT640D for inverting.
Mounting Holes M3
The difference between the SN74LVCC4245ANSR and the SN74LVCC3245BNSR is the switched 5V and 3V3 Rails.

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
